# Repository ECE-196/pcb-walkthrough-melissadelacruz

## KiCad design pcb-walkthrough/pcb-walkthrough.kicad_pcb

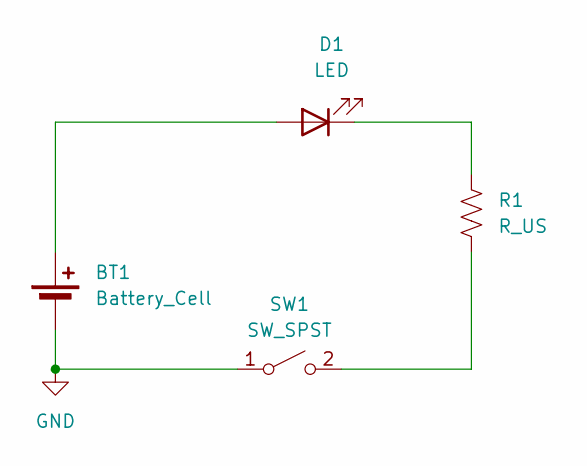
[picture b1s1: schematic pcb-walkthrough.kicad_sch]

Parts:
BT1: Battery_Cell; BatteryHolder_Keystone_103_1x20mm
D1: LED; LED_2512_6332Metric
R1: R_US; R_2512_6332Metric
SW1: SW_SPST; SW_PUSH_6mm

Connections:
GND: BT1.2 (-), SW1.1 (A)
unnamed: BT1.1 (+), D1.2 (A)
unnamed: D1.1 (K), R1.1
unnamed: R1.2, SW1.2 (B)

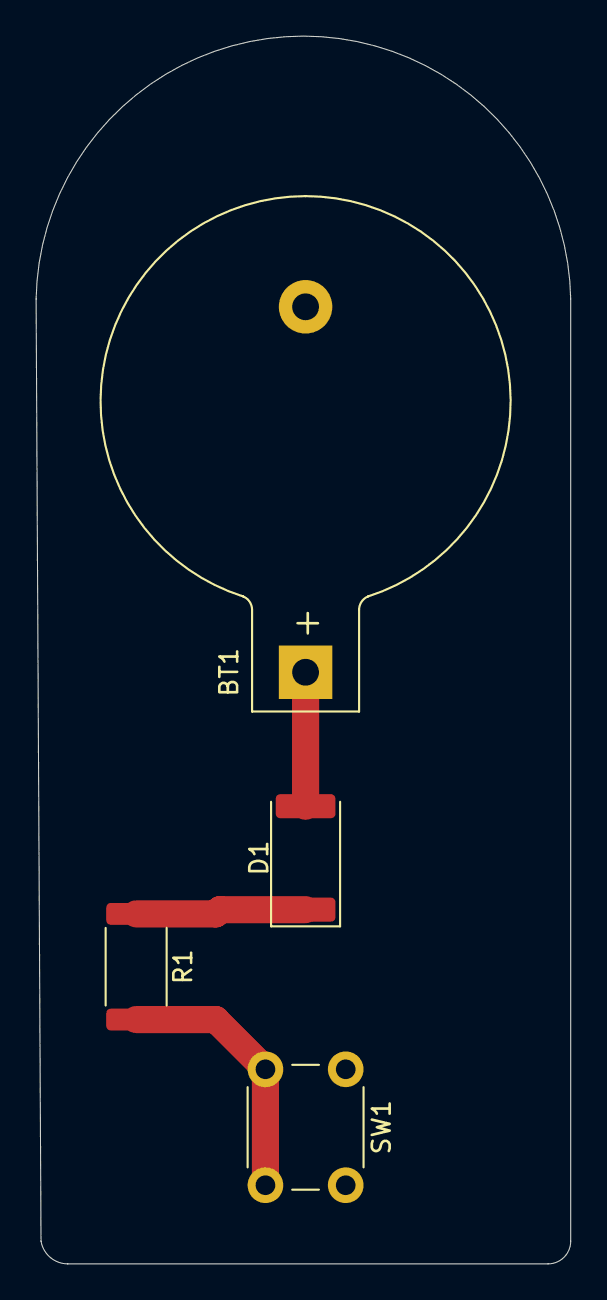
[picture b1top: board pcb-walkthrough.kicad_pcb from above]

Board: 2 copper layers, 30.0 x 68.8 mm, 4 parts (0 on the bottom side), 4 nets.

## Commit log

2024-10-08 add deadline
2024-10-13 Updated Files
2024-10-13 PCB Walkthrough Melissa
